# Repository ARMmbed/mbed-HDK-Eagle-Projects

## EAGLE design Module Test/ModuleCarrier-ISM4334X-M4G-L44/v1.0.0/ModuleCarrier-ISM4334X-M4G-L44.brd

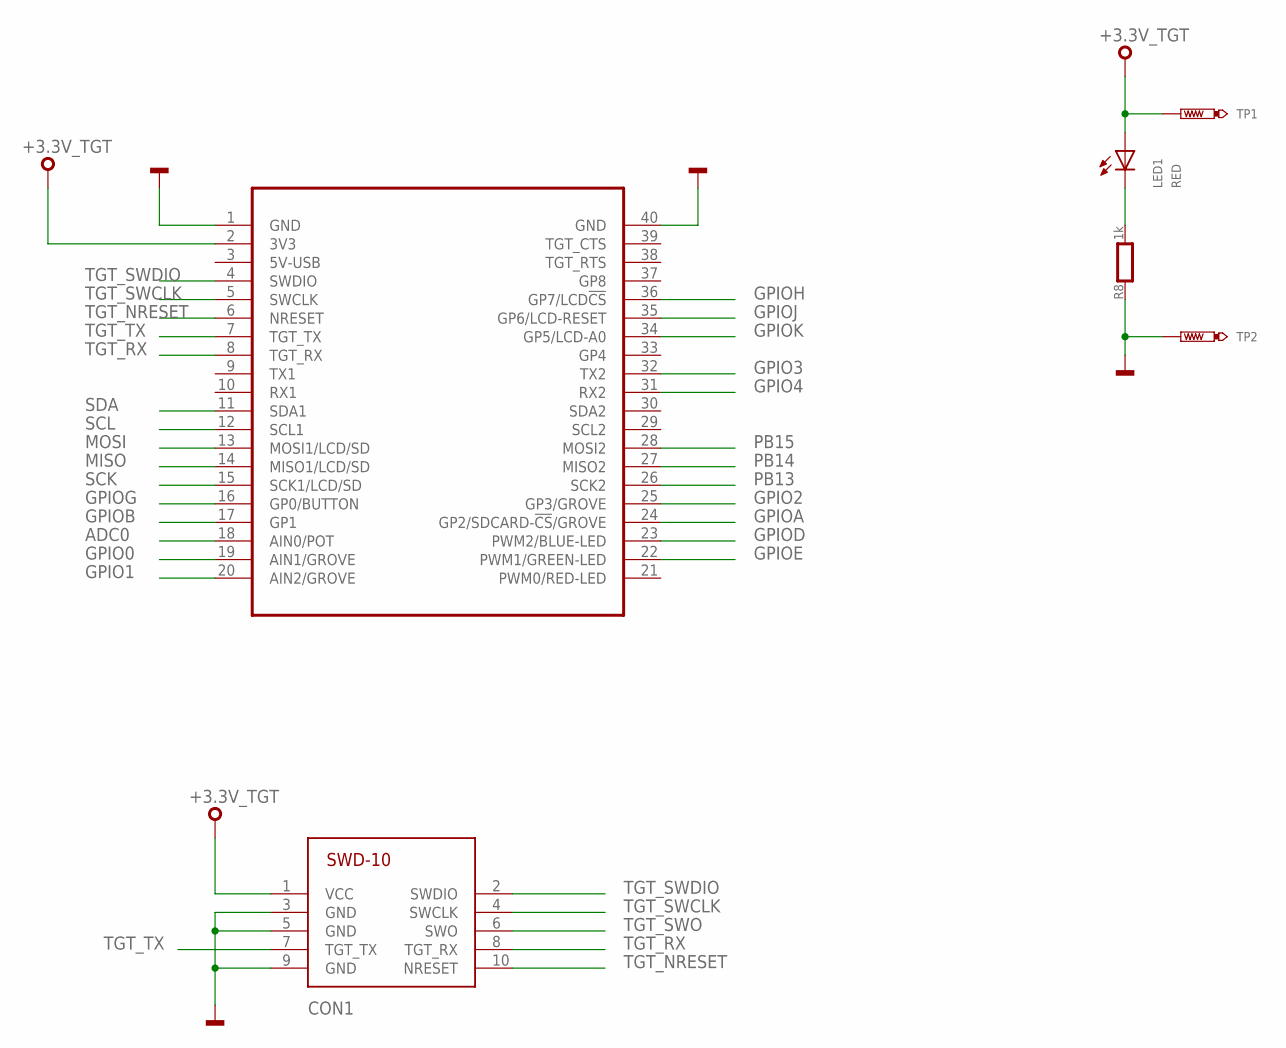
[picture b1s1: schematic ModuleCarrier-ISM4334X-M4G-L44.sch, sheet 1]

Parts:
CON1: SWD-10/TC2050_SMD; FTSH-105-02
LED1: RED; CHIPLED_0603
MOD2: MODULE_DAUGHTER
R8: 1k; 0603
TP1, TP2: TEST-POINT-50R-PTH; TP50-PTH

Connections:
+3.3V_TGT: CON1.1 (VCC), LED1.A, MOD2.2 (3V3), TP1.TP; also elsewhere on the board
ADC0: MOD2.18 (AIN0/POT); also elsewhere on the board
GND: CON1.3 (GND), CON1.5 (GND), CON1.9 (GND), MOD2.1 (GND), MOD2.40 (GND), R8.1, TP2.TP; also elsewhere on the board
GPIO0: MOD2.19 (AIN1/GROVE); also elsewhere on the board
GPIO1: MOD2.20 (AIN2/GROVE); also elsewhere on the board
GPIO2: MOD2.25 (GP3/GROVE); also elsewhere on the board
GPIO3: MOD2.32 (TX2); also elsewhere on the board
GPIO4: MOD2.31 (RX2); also elsewhere on the board
GPIOA: MOD2.24 (GP2/SDCARD-!CS!/GROVE); also elsewhere on the board
GPIOB: MOD2.17 (GP1); also elsewhere on the board
GPIOD: MOD2.23 (PWM2/BLUE-LED); also elsewhere on the board
GPIOE: MOD2.22 (PWM1/GREEN-LED); also elsewhere on the board
GPIOG: MOD2.16 (GP0/BUTTON); also elsewhere on the board
GPIOH: MOD2.36 (GP7/LCD!CS); also elsewhere on the board
GPIOJ: MOD2.35 (GP6/LCD-RESET); also elsewhere on the board
GPIOK: MOD2.34 (GP5/LCD-A0); also elsewhere on the board
MISO: MOD2.14 (MISO1/LCD/SD); also elsewhere on the board
MOSI: MOD2.13 (MOSI1/LCD/SD); also elsewhere on the board
PA_1: LED1.C, R8.2
PB13: MOD2.26 (SCK2); also elsewhere on the board
PB14: MOD2.27 (MISO2); also elsewhere on the board
PB15: MOD2.28 (MOSI2); also elsewhere on the board
SCK: MOD2.15 (SCK1/LCD/SD); also elsewhere on the board
SCL: MOD2.12 (SCL1); also elsewhere on the board
SDA: MOD2.11 (SDA1); also elsewhere on the board
TGT_NRESET: CON1.10 (NRESET), MOD2.6 (NRESET); also elsewhere on the board
TGT_RX: CON1.8 (TGT_RX), MOD2.8 (TGT_RX); also elsewhere on the board
TGT_SWCLK: CON1.4 (SWCLK), MOD2.5 (SWCLK); also elsewhere on the board
TGT_SWDIO: CON1.2 (SWDIO), MOD2.4 (SWDIO); also elsewhere on the board
TGT_SWO: CON1.6 (SWO); also elsewhere on the board
TGT_TX: CON1.7 (TGT_TX), MOD2.7 (TGT_TX); also elsewhere on the board

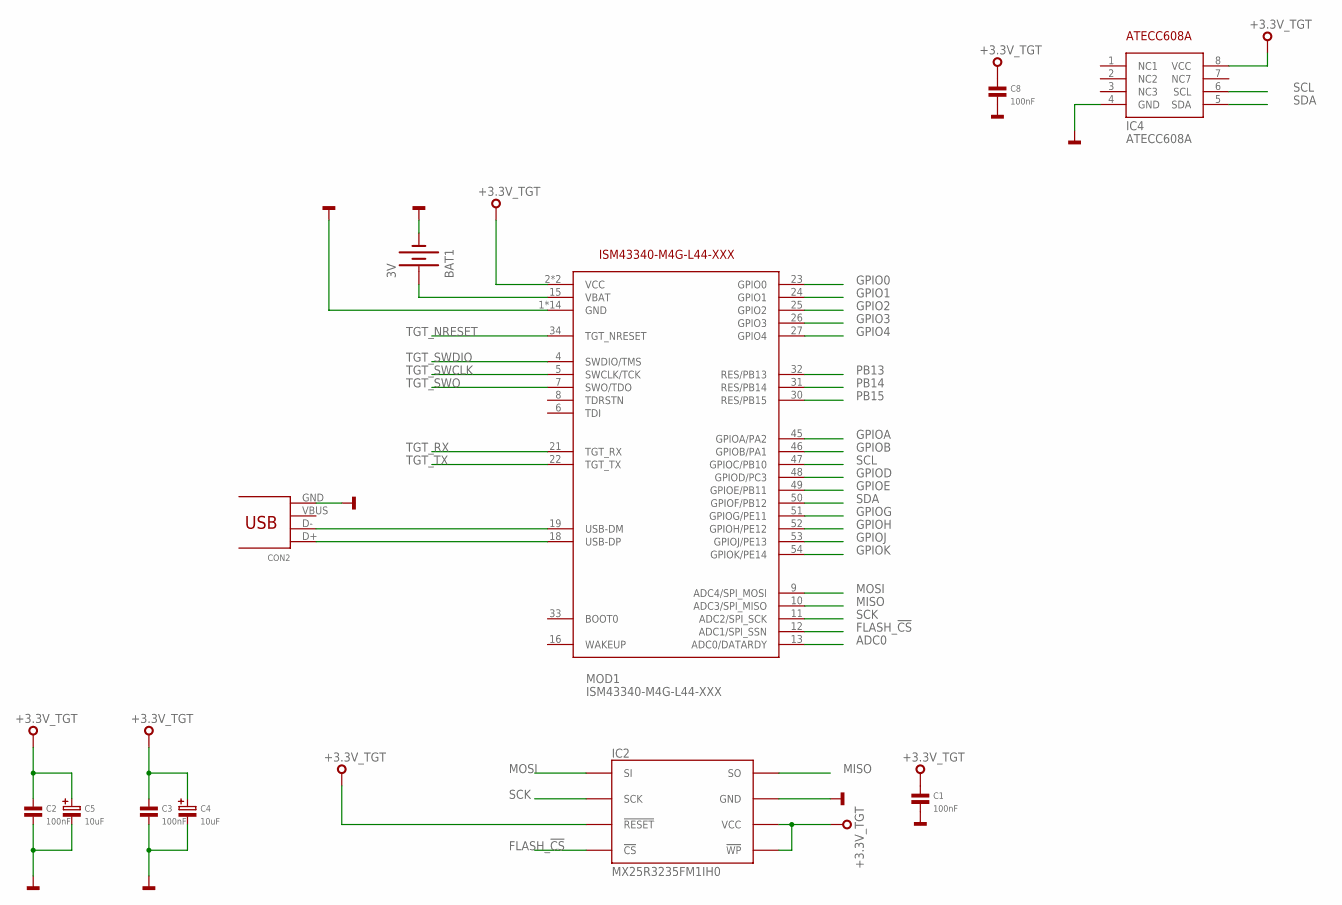
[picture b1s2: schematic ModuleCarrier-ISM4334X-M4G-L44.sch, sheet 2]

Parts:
BAT1: 3V; BATTCON_12MM
C1, C2, C3, C8: 100nF; 0603
C4, C5: 10uF; SMC_B
CON2: 10033526-N3212MLF; USB-MINI-B-H
IC2: MX25R3235FM1IH0; SO8
IC4: ATECC608A; SO8
MOD1: ISM43340-M4G-L44-XXX

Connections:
+3.3V_TGT: C1.1, C2.1, C3.1, C4.+, C5.+, C8.1, IC2.3 (!WP), IC2.7 (!RESET), IC2.8 (VCC), IC4.8 (VCC), MOD1.2 (VCC), MOD1.14 (VCC); also elsewhere on the board
ADC0: MOD1.13 (ADC0/DATARDY); also elsewhere on the board
FLASH_!CS: IC2.1 (!CS), MOD1.12 (ADC1/SPI_SSN)
GND: BAT1.GND (-), C1.2, C2.2, C3.2, C4.-, C5.-, C8.2, CON2.GND, IC2.4 (GND), IC4.4 (GND), MOD1.1 (GND), MOD1.3 (GND), MOD1.17 (GND), MOD1.20 (GND), MOD1.35 (GND), MOD1.36 (GND), MOD1.37 (GND), MOD1.38 (GND), MOD1.39 (GND), MOD1.40 (GND), MOD1.41 (GND), MOD1.42 (GND), MOD1.43 (GND), MOD1.44 (GND); also elsewhere on the board
GPIO0: MOD1.23 (GPIO0); also elsewhere on the board
GPIO1: MOD1.24 (GPIO1); also elsewhere on the board
GPIO2: MOD1.25 (GPIO2); also elsewhere on the board
GPIO3: MOD1.26 (GPIO3); also elsewhere on the board
GPIO4: MOD1.27 (GPIO4); also elsewhere on the board
GPIOA: MOD1.45 (GPIOA/PA2); also elsewhere on the board
GPIOB: MOD1.46 (GPIOB/PA1); also elsewhere on the board
GPIOD: MOD1.48 (GPIOD/PC3); also elsewhere on the board
GPIOE: MOD1.49 (GPIOE/PB11); also elsewhere on the board
GPIOG: MOD1.51 (GPIOG/PE11); also elsewhere on the board
GPIOH: MOD1.52 (GPIOH/PE12); also elsewhere on the board
GPIOJ: MOD1.53 (GPIOJ/PE13); also elsewhere on the board
GPIOK: MOD1.54 (GPIOK/PE14); also elsewhere on the board
MISO: IC2.2 (SO), MOD1.10 (ADC3/SPI_MISO); also elsewhere on the board
MOSI: IC2.5 (SI), MOD1.9 (ADC4/SPI_MOSI); also elsewhere on the board
unnamed: CON2.D+, MOD1.18 (USB-DP)
unnamed: CON2.D-, MOD1.19 (USB-DM)
unnamed: BAT1.PWR@1 (+), MOD1.15 (VBAT)
PB13: MOD1.32 (RES/PB13); also elsewhere on the board
PB14: MOD1.31 (RES/PB14); also elsewhere on the board
PB15: MOD1.30 (RES/PB15); also elsewhere on the board
SCK: IC2.6 (SCK), MOD1.11 (ADC2/SPI_SCK); also elsewhere on the board
SCL: IC4.6 (SCL), MOD1.47 (GPIOC/PB10); also elsewhere on the board
SDA: IC4.5 (SDA), MOD1.50 (GPIOF/PB12); also elsewhere on the board
TGT_NRESET: MOD1.34 (TGT_NRESET); also elsewhere on the board
TGT_RX: MOD1.21 (TGT_RX); also elsewhere on the board
TGT_SWCLK: MOD1.5 (SWCLK/TCK); also elsewhere on the board
TGT_SWDIO: MOD1.4 (SWDIO/TMS); also elsewhere on the board
TGT_SWO: MOD1.7 (SWO/TDO); also elsewhere on the board
TGT_TX: MOD1.22 (TGT_TX); also elsewhere on the board

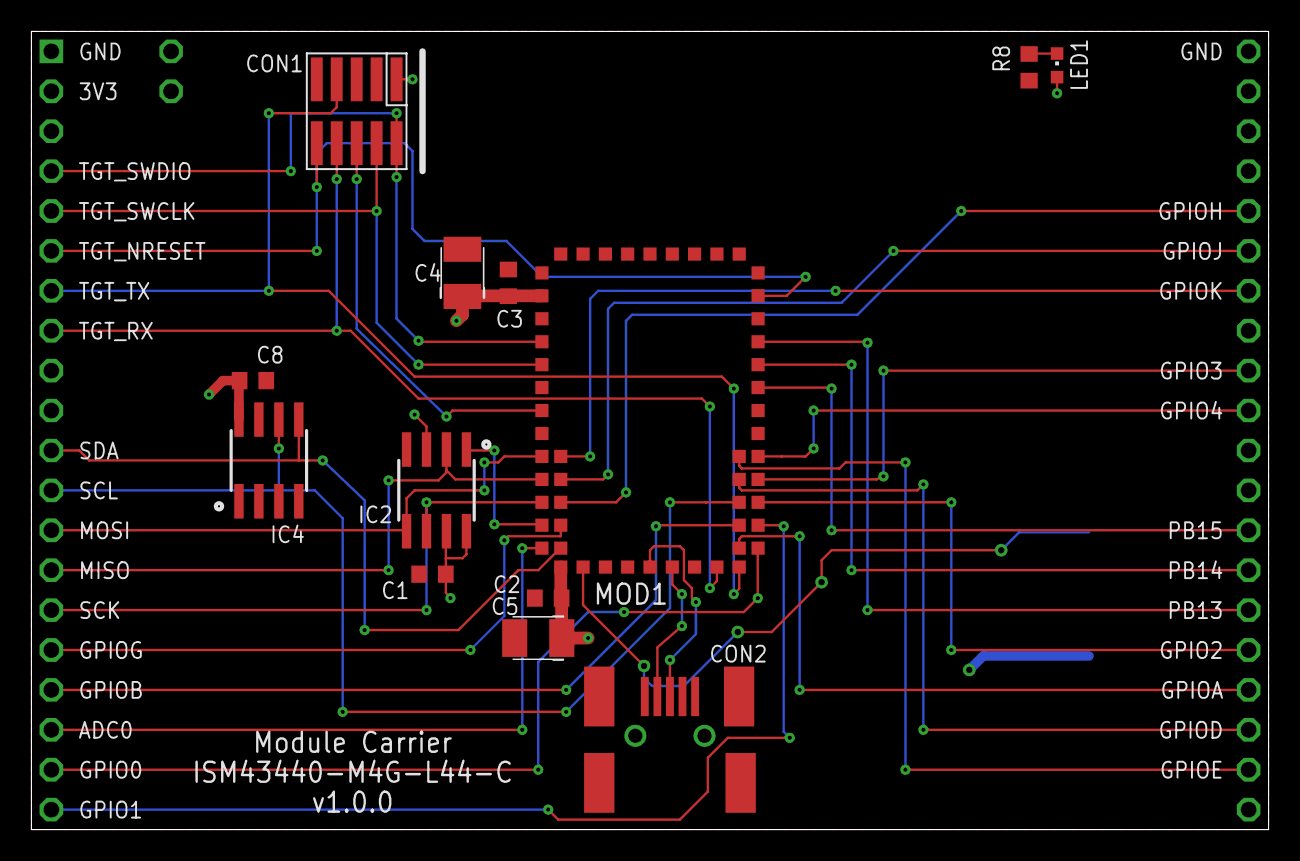
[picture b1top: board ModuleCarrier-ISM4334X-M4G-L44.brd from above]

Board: 2 copper layers, 78.7 x 50.8 mm, 17 parts (1 on the bottom side), 35 nets.

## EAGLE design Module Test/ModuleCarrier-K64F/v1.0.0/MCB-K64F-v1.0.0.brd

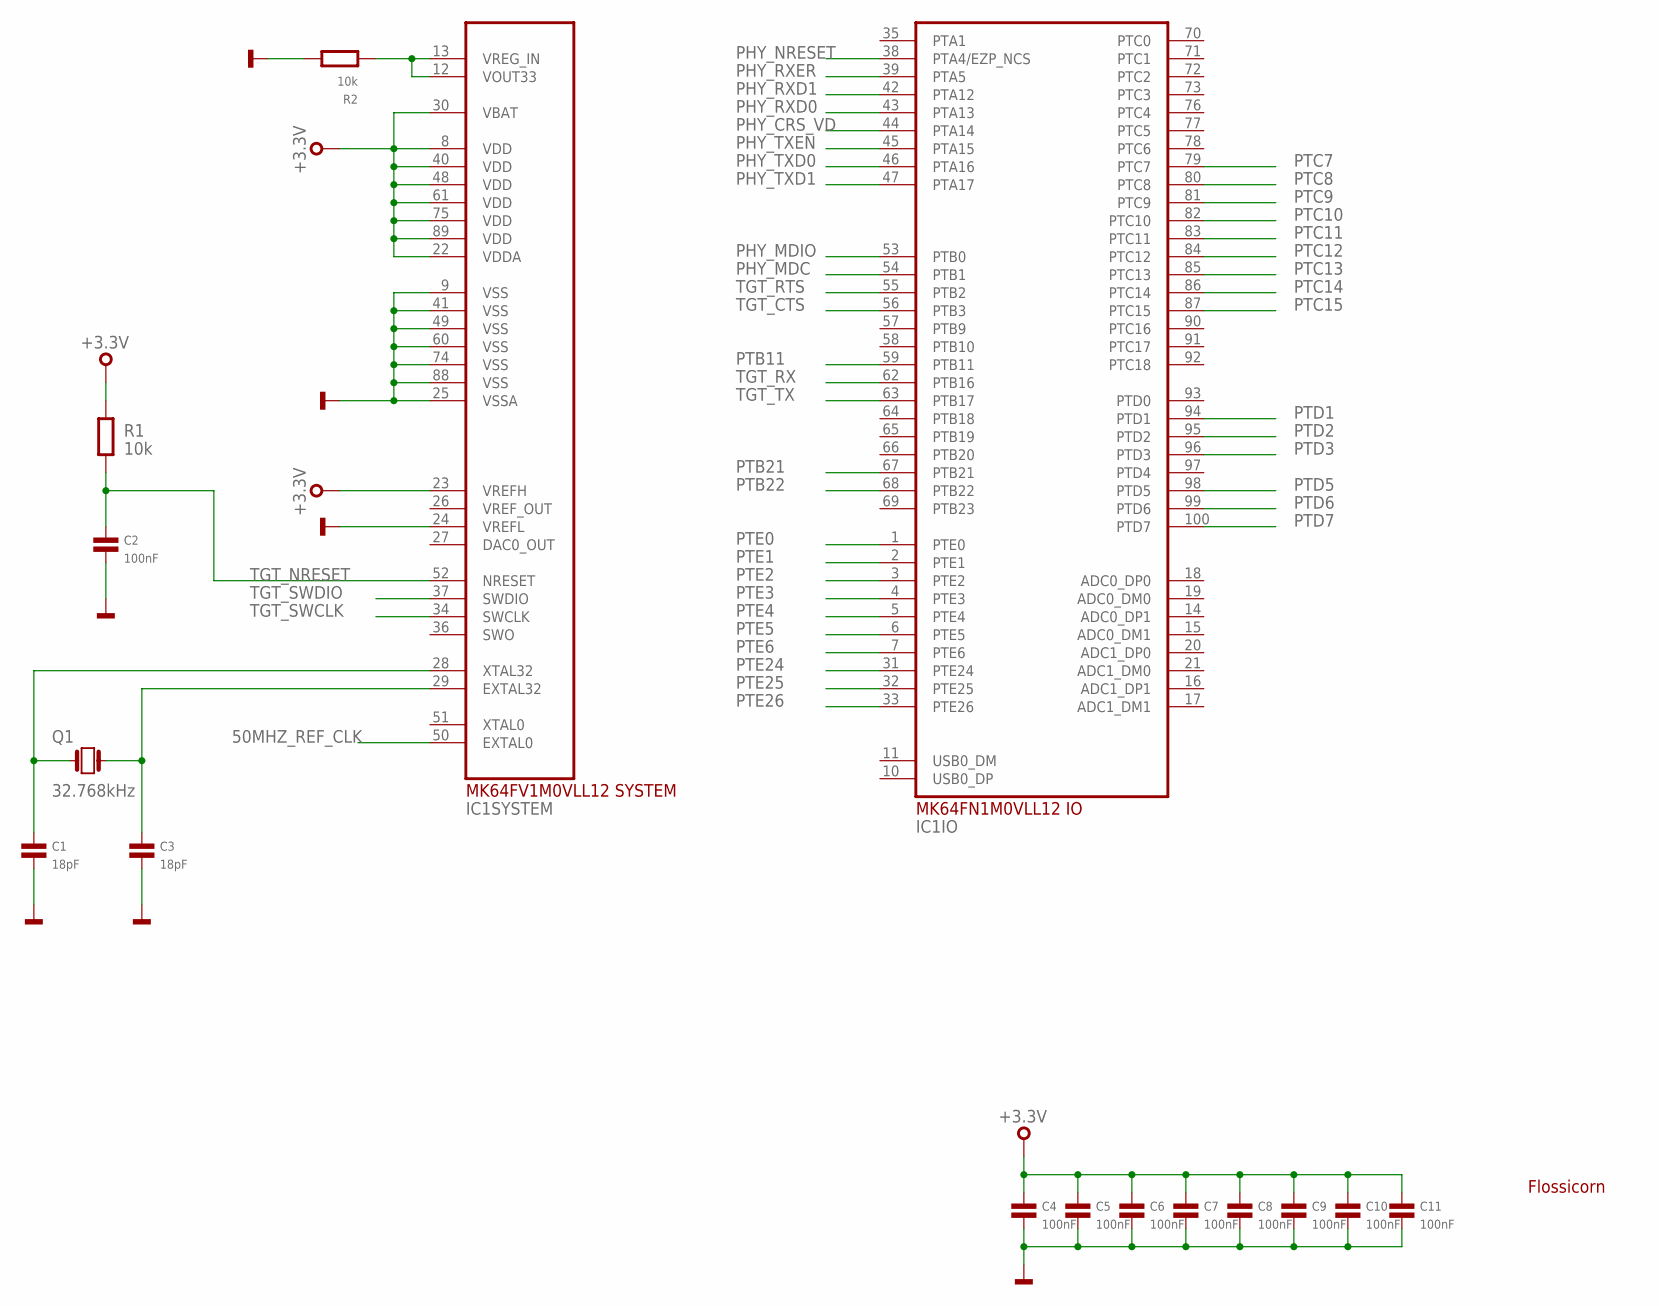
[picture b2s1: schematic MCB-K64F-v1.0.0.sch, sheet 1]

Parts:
C1, C3: 18pF; 0603
C2, C4, C5, C6, C7, C8, C9, C10, C11: 100nF; 0603
IC1: MK64FN1M0VLL12; LQFP100
Q1: 32.768kHz; FC135
R1, R2: 10k; 0603
SS1: FLOSSICORN0.5; FLOSSICORN-0.5

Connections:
50MHZ_REF_CLK: IC1.50 (EXTAL0); also elsewhere on the board
+3.3V: C4.1, C5.1, C6.1, C7.1, C8.1, C9.1, C10.1, C11.1, IC1.8 (VDD), IC1.22 (VDDA), IC1.23 (VREFH), IC1.30 (VBAT), IC1.40 (VDD), IC1.48 (VDD), IC1.61 (VDD), IC1.75 (VDD), IC1.89 (VDD), R1.2; also elsewhere on the board
GND: C1.2, C2.2, C3.2, C4.2, C5.2, C6.2, C7.2, C8.2, C9.2, C10.2, C11.2, IC1.9 (VSS), IC1.24 (VREFL), IC1.25 (VSSA), IC1.41 (VSS), IC1.49 (VSS), IC1.60 (VSS), IC1.74 (VSS), IC1.88 (VSS), R2.2; also elsewhere on the board
unnamed: C1.1, IC1.28 (XTAL32), Q1.X1 (1)
unnamed: C3.1, IC1.29 (EXTAL32), Q1.X2 (2)
unnamed: IC1.12 (VOUT33), IC1.13 (VREG_IN), R2.1
PHY_CRS_VD: IC1.44 (PTA14); also elsewhere on the board
PHY_MDC: IC1.54 (PTB1); also elsewhere on the board
PHY_MDIO: IC1.53 (PTB0); also elsewhere on the board
PHY_NRESET: IC1.38 (PTA4/EZP_NCS); also elsewhere on the board
PHY_RXD0: IC1.43 (PTA13); also elsewhere on the board
PHY_RXD1: IC1.42 (PTA12); also elsewhere on the board
PHY_RXER: IC1.39 (PTA5); also elsewhere on the board
PHY_TXD0: IC1.46 (PTA16); also elsewhere on the board
PHY_TXD1: IC1.47 (PTA17); also elsewhere on the board
PHY_TXEN: IC1.45 (PTA15); also elsewhere on the board
PTB11: IC1.59 (PTB11); also elsewhere on the board
PTB21: IC1.67 (PTB21); also elsewhere on the board
PTB22: IC1.68 (PTB22); also elsewhere on the board
PTC7: IC1.79 (PTC7); also elsewhere on the board
PTC8: IC1.80 (PTC8); also elsewhere on the board
PTC9: IC1.81 (PTC9); also elsewhere on the board
PTC10: IC1.82 (PTC10); also elsewhere on the board
PTC11: IC1.83 (PTC11); also elsewhere on the board
PTC12: IC1.84 (PTC12); also elsewhere on the board
PTC13: IC1.85 (PTC13); also elsewhere on the board
PTC14: IC1.86 (PTC14); also elsewhere on the board
PTC15: IC1.87 (PTC15); also elsewhere on the board
PTD1: IC1.94 (PTD1); also elsewhere on the board
PTD2: IC1.95 (PTD2); also elsewhere on the board
PTD3: IC1.96 (PTD3); also elsewhere on the board
PTD5: IC1.98 (PTD5); also elsewhere on the board
PTD6: IC1.99 (PTD6); also elsewhere on the board
PTD7: IC1.100 (PTD7); also elsewhere on the board
PTE0: IC1.1 (PTE0); also elsewhere on the board
PTE1: IC1.2 (PTE1); also elsewhere on the board
PTE2: IC1.3 (PTE2); also elsewhere on the board
PTE3: IC1.4 (PTE3); also elsewhere on the board
PTE4: IC1.5 (PTE4); also elsewhere on the board
PTE5: IC1.6 (PTE5); also elsewhere on the board
PTE6: IC1.7 (PTE6); also elsewhere on the board
PTE24: IC1.31 (PTE24); also elsewhere on the board
PTE25: IC1.32 (PTE25); also elsewhere on the board
PTE26: IC1.33 (PTE26); also elsewhere on the board
TGT_CTS: IC1.56 (PTB3); also elsewhere on the board
TGT_NRESET: C2.1, IC1.52 (NRESET), R1.1; also elsewhere on the board
TGT_RTS: IC1.55 (PTB2); also elsewhere on the board
TGT_RX: IC1.62 (PTB16); also elsewhere on the board
TGT_SWCLK: IC1.34 (SWCLK); also elsewhere on the board
TGT_SWDIO: IC1.37 (SWDIO); also elsewhere on the board
TGT_TX: IC1.63 (PTB17); also elsewhere on the board

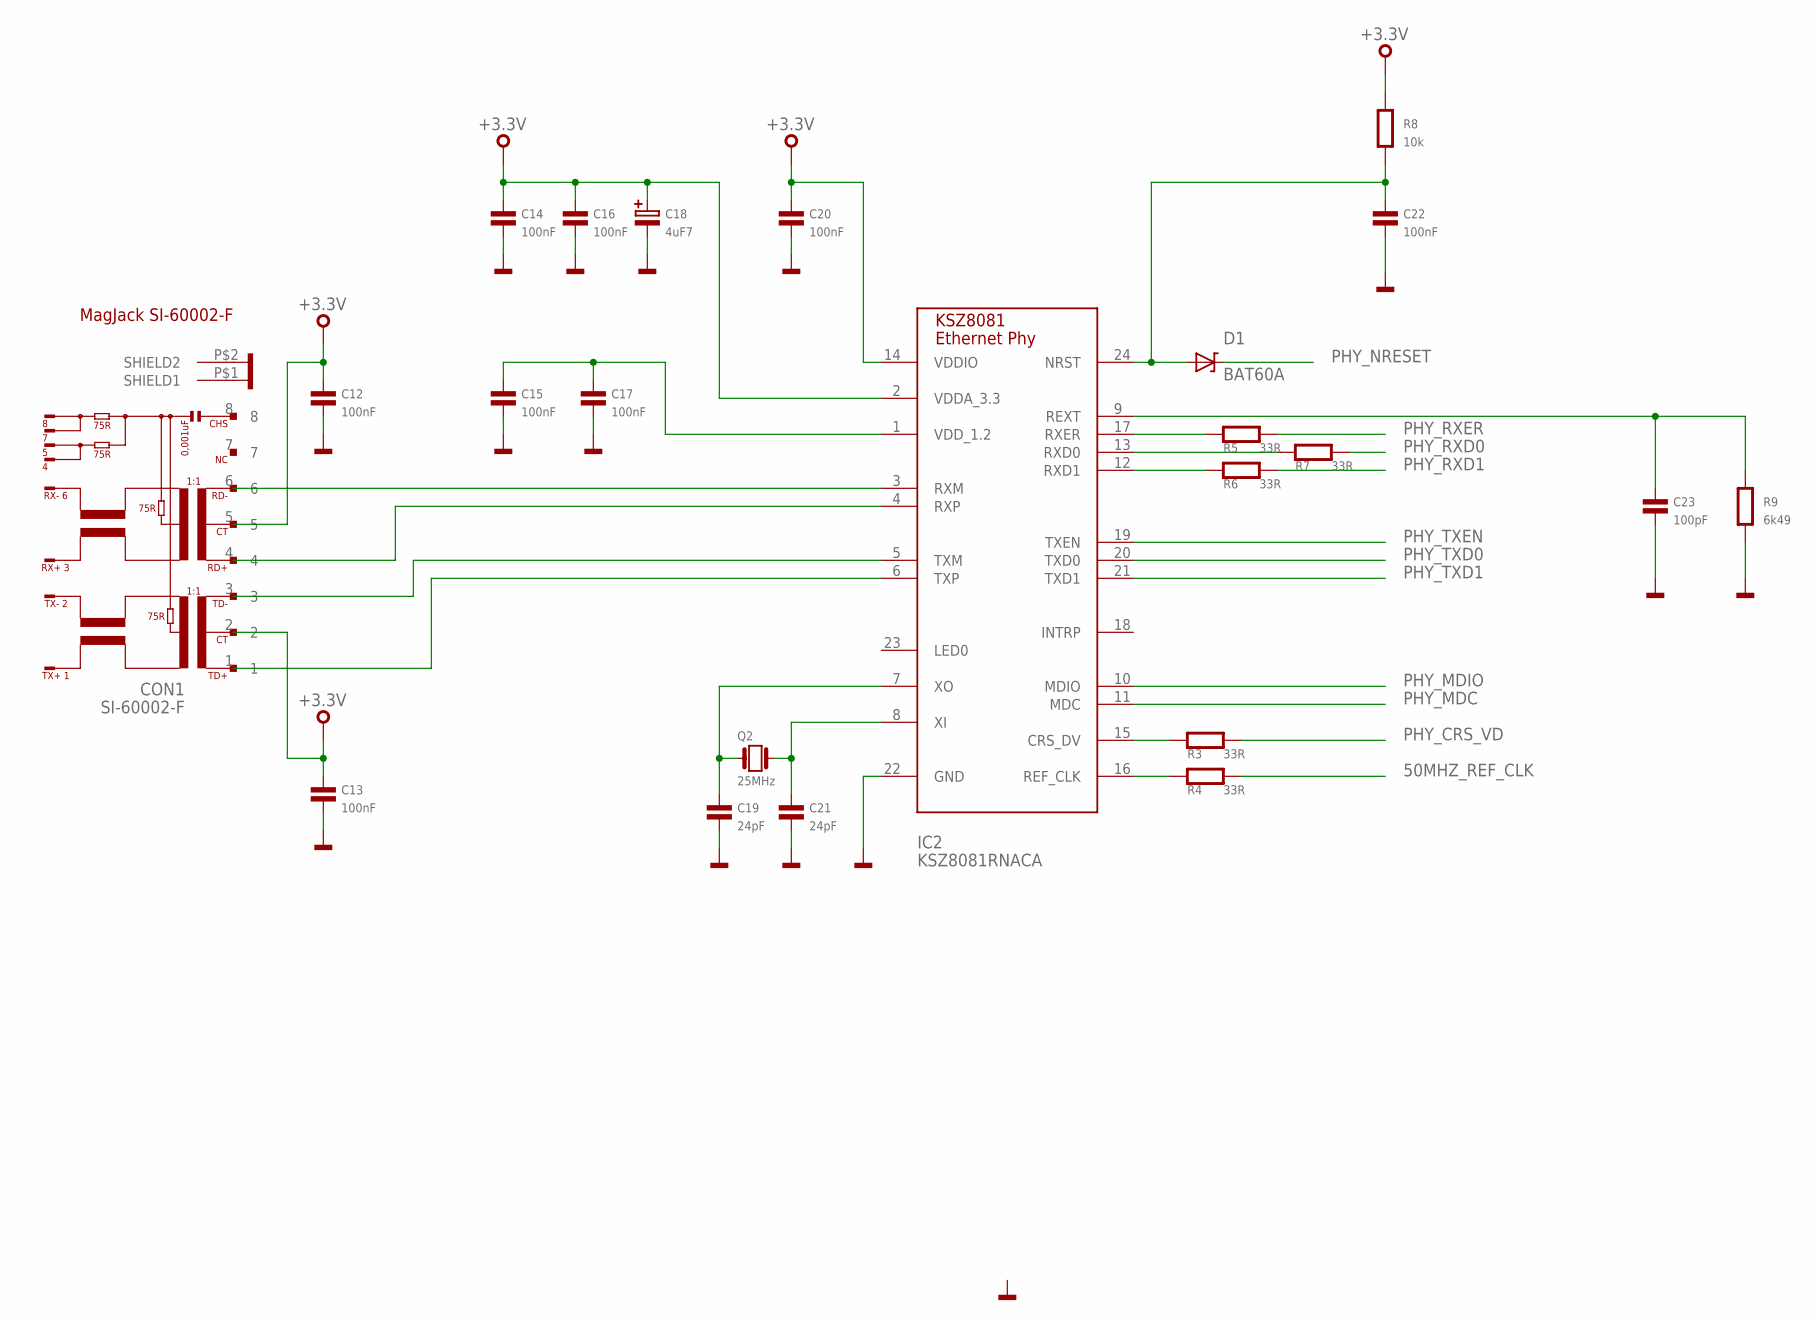
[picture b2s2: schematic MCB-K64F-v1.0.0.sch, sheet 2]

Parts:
C12, C13, C14, C15, C16, C17, C20, C22: 100nF; 0603
C18: 4uF7; SMC_A
C19, C21: 24pF; 0603
C23: 100pF; 0603
CON1: SI-60002-F; RJ45
D1: BAT60A
IC2: KSZ8081RNACA; QFN-24
Q2: 25MHz; 3.2X.2.5
R3, R4, R5, R6, R7: 33R; 0603
R8: 10k; 0603
R9: 6k49; 0603

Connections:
50MHZ_REF_CLK: R4.2; also elsewhere on the board
+3.3V: C12.1, C13.1, C14.1, C16.1, C18.+, C20.1, CON1.2, CON1.5, IC2.2 (VDDA_3.3), IC2.14 (VDDIO), R8.2; also elsewhere on the board
GND: C12.2, C13.2, C14.2, C15.2, C16.2, C17.2, C18.-, C19.2, C20.2, C21.2, C22.2, C23.2, CON1.P$1 (SHIELD1), CON1.P$2 (SHIELD2), IC2.22 (GND), R9.1; also elsewhere on the board
unnamed: IC2.16 (REF_CLK), R4.1
unnamed: CON1.6, IC2.3 (RXM)
unnamed: CON1.4, IC2.4 (RXP)
unnamed: CON1.3, IC2.5 (TXM)
unnamed: CON1.1, IC2.6 (TXP)
unnamed: C19.1, IC2.7 (XO), Q2.P$1 (1)
unnamed: C21.1, IC2.8 (XI), Q2.P$3 (2)
unnamed: IC2.12 (RXD1), R6.1
unnamed: IC2.13 (RXD0), R7.1
unnamed: IC2.17 (RXER), R5.1
unnamed: IC2.15 (CRS_DV), R3.1
unnamed: C22.1, D1.A, IC2.24 (NRST), R8.1
unnamed: C15.1, C17.1, IC2.1 (VDD_1.2)
unnamed: C23.1, IC2.9 (REXT), R9.2
PHY_CRS_VD: R3.2; also elsewhere on the board
PHY_MDC: IC2.11 (MDC); also elsewhere on the board
PHY_MDIO: IC2.10 (MDIO); also elsewhere on the board
PHY_NRESET: D1.K; also elsewhere on the board
PHY_RXD0: R7.2; also elsewhere on the board
PHY_RXD1: R6.2; also elsewhere on the board
PHY_RXER: R5.2; also elsewhere on the board
PHY_TXD0: IC2.20 (TXD0); also elsewhere on the board
PHY_TXD1: IC2.21 (TXD1); also elsewhere on the board
PHY_TXEN: IC2.19 (TXEN); also elsewhere on the board

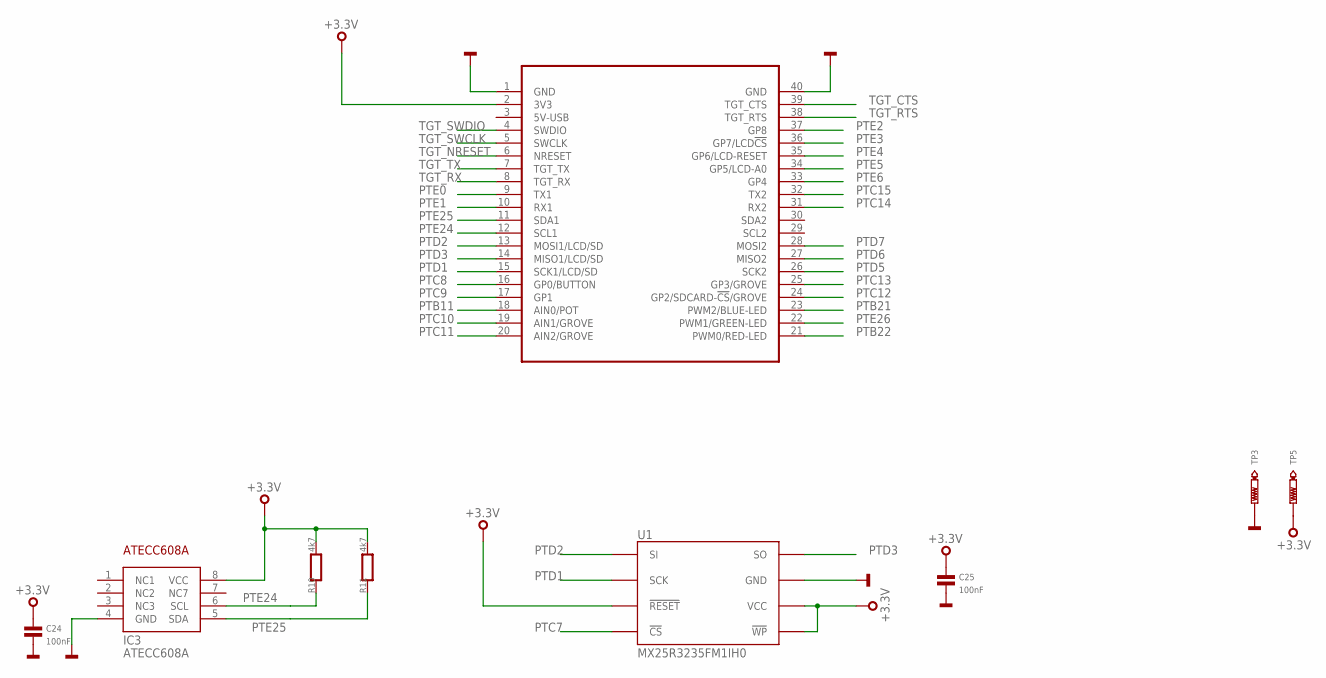
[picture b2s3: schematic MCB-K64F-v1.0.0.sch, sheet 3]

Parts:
C24, C25: 100nF; 0603
IC3: ATECC608A; SO8
MOD1: MODULE_DAUGHTER
R10, R11: 4k7; 0603
TP3, TP5: TEST-POINT-50R-PTH; TP50-PTH
U1: MX25R3235FM1IH0; SO8

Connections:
+3.3V: C24.1, C25.1, IC3.8 (VCC), MOD1.2 (3V3), R10.2, R11.2, TP5.TP, U1.3 (!WP), U1.7 (!RESET), U1.8 (VCC); also elsewhere on the board
GND: C24.2, C25.2, IC3.4 (GND), MOD1.1 (GND), MOD1.40 (GND), TP3.TP, U1.4 (GND); also elsewhere on the board
PTB11: MOD1.18 (AIN0/POT); also elsewhere on the board
PTB21: MOD1.23 (PWM2/BLUE-LED); also elsewhere on the board
PTB22: MOD1.21 (PWM0/RED-LED); also elsewhere on the board
PTC7: U1.1 (!CS); also elsewhere on the board
PTC8: MOD1.16 (GP0/BUTTON); also elsewhere on the board
PTC9: MOD1.17 (GP1); also elsewhere on the board
PTC10: MOD1.19 (AIN1/GROVE); also elsewhere on the board
PTC11: MOD1.20 (AIN2/GROVE); also elsewhere on the board
PTC12: MOD1.24 (GP2/SDCARD-!CS!/GROVE); also elsewhere on the board
PTC13: MOD1.25 (GP3/GROVE); also elsewhere on the board
PTC14: MOD1.31 (RX2); also elsewhere on the board
PTC15: MOD1.32 (TX2); also elsewhere on the board
PTD1: MOD1.15 (SCK1/LCD/SD), U1.6 (SCK); also elsewhere on the board
PTD2: MOD1.13 (MOSI1/LCD/SD), U1.5 (SI); also elsewhere on the board
PTD3: MOD1.14 (MISO1/LCD/SD), U1.2 (SO); also elsewhere on the board
PTD5: MOD1.26 (SCK2); also elsewhere on the board
PTD6: MOD1.27 (MISO2); also elsewhere on the board
PTD7: MOD1.28 (MOSI2); also elsewhere on the board
PTE0: MOD1.9 (TX1); also elsewhere on the board
PTE1: MOD1.10 (RX1); also elsewhere on the board
PTE2: MOD1.37 (GP8); also elsewhere on the board
PTE3: MOD1.36 (GP7/LCD!CS); also elsewhere on the board
PTE4: MOD1.35 (GP6/LCD-RESET); also elsewhere on the board
PTE5: MOD1.34 (GP5/LCD-A0); also elsewhere on the board
PTE6: MOD1.33 (GP4); also elsewhere on the board
PTE24: IC3.6 (SCL), MOD1.12 (SCL1), R10.1; also elsewhere on the board
PTE25: IC3.5 (SDA), MOD1.11 (SDA1), R11.1; also elsewhere on the board
PTE26: MOD1.22 (PWM1/GREEN-LED); also elsewhere on the board
TGT_CTS: MOD1.39 (TGT_CTS); also elsewhere on the board
TGT_NRESET: MOD1.6 (NRESET); also elsewhere on the board
TGT_RTS: MOD1.38 (TGT_RTS); also elsewhere on the board
TGT_RX: MOD1.8 (TGT_RX); also elsewhere on the board
TGT_SWCLK: MOD1.5 (SWCLK); also elsewhere on the board
TGT_SWDIO: MOD1.4 (SWDIO); also elsewhere on the board
TGT_TX: MOD1.7 (TGT_TX); also elsewhere on the board

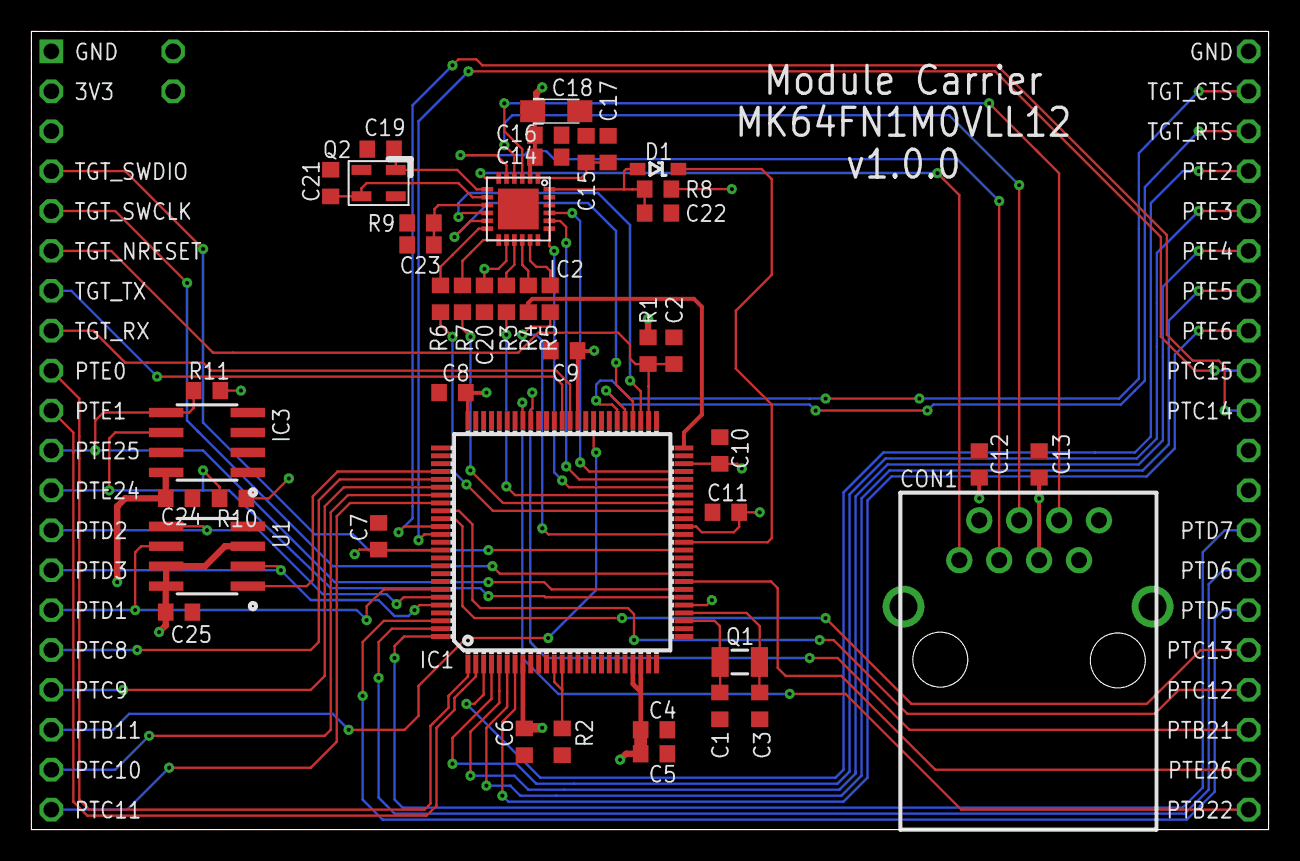
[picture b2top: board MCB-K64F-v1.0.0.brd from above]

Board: 2 copper layers, 78.7 x 50.8 mm, 48 parts (0 on the bottom side), 65 nets.

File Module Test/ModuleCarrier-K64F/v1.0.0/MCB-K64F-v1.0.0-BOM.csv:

"Qty";"Value";"Device";"Package";"Parts";"Description";"MF";"MFN";"OC-DIGIKEY";"OC-MOUSER";"OC-NEWARK";
"17";"100nF";"C0603";"0603";"C2, C4, C5, C6, C7, C8, C9, C10, C11, C12, C13, C14, C15, C16, C17, C20, C22";"Capacitor";"";"";"";"";"";
"2";"100nF";"CAPACITOR0603";"0603";"C24, C25";"Capacitor";"";"";"";"";"";
"1";"100pF";"C0603";"0603";"C23";"Capacitor";"";"";"";"";"";
"3";"10k";"R0603";"0603";"R1, R2, R8";"";"";"";"";"";"";
"2";"18pF";"C0603";"0603";"C1, C3";"Capacitor";"";"";"";"";"";
"2";"24pF";"C0603";"0603";"C19, C21";"Capacitor";"";"";"";"";"";
"1";"25MHz";"Q_3.2X2.5";"3.2X.2.5";"Q2";"";"";"";"";"";"";
"1";"32.768kHz";"Q_FC135";"FC135";"Q1";"";"";"";"";"";"";
"5";"33R";"R0603";"0603";"R3, R4, R5, R6, R7";"";"";"";"";"";"";
"2";"4k7";"RESISTOR0603";"0603";"R10, R11";"Resistor";"";"";"";"";"";
"1";"4uF7";"C-POLA";"SMC_A";"C18";"Polarised capacitor";"";"";"";"";"";
"1";"6k49";"R0603";"0603";"R9";"";"";"";"";"";"";
"1";"ATECC608A";"ATECC608A";"SO8";"IC3";"";"";"";"";"";"";
"1";"BAT60A";"BAT60A";"BAT60A";"D1";"Schottky Diode";"";"";"";"";"";
"1";"FLOSSICORN0.5";"FLOSSICORN0.5";"FLOSSICORN-0.5";"SS1";"";"";"";"";"";"";
"1";"KSZ8081RNACA";"KSZ8081RNACA";"QFN-24";"IC2";"";"";"";"";"";"";
"1";"MK64FN1M0VLL12";"MK64FN1M0VLL12";"LQFP100";"IC1";"";"";"";"";"";"";
"1";"MODULE_DAUGHTER";"MODULE_DAUGHTER";"MODULE_DAUGHTER";"MOD1";"";"";"";"";"";"";
"1";"MX25R3235FM1IH0";"MX25R3235FM1IH0";"SO8";"U1";"Serial Flash 32 Mb 80 Mhz";"Macronix";"MX25R3235FM2IH0";"1092-1174-ND";"";"";
"1";"SI-60002-F";"SI-60002-F";"RJ45";"CON1";"RJ45 Right Angle";"Stewart Connector";"SI-60002-F";"380-1105-ND";"";"24M7449";
"2";"TEST-POINT-50R-PTH";"TEST-POINT-50R-PTH";"TP50-PTH";"TP3, TP5";"";"";"";"";"";"";

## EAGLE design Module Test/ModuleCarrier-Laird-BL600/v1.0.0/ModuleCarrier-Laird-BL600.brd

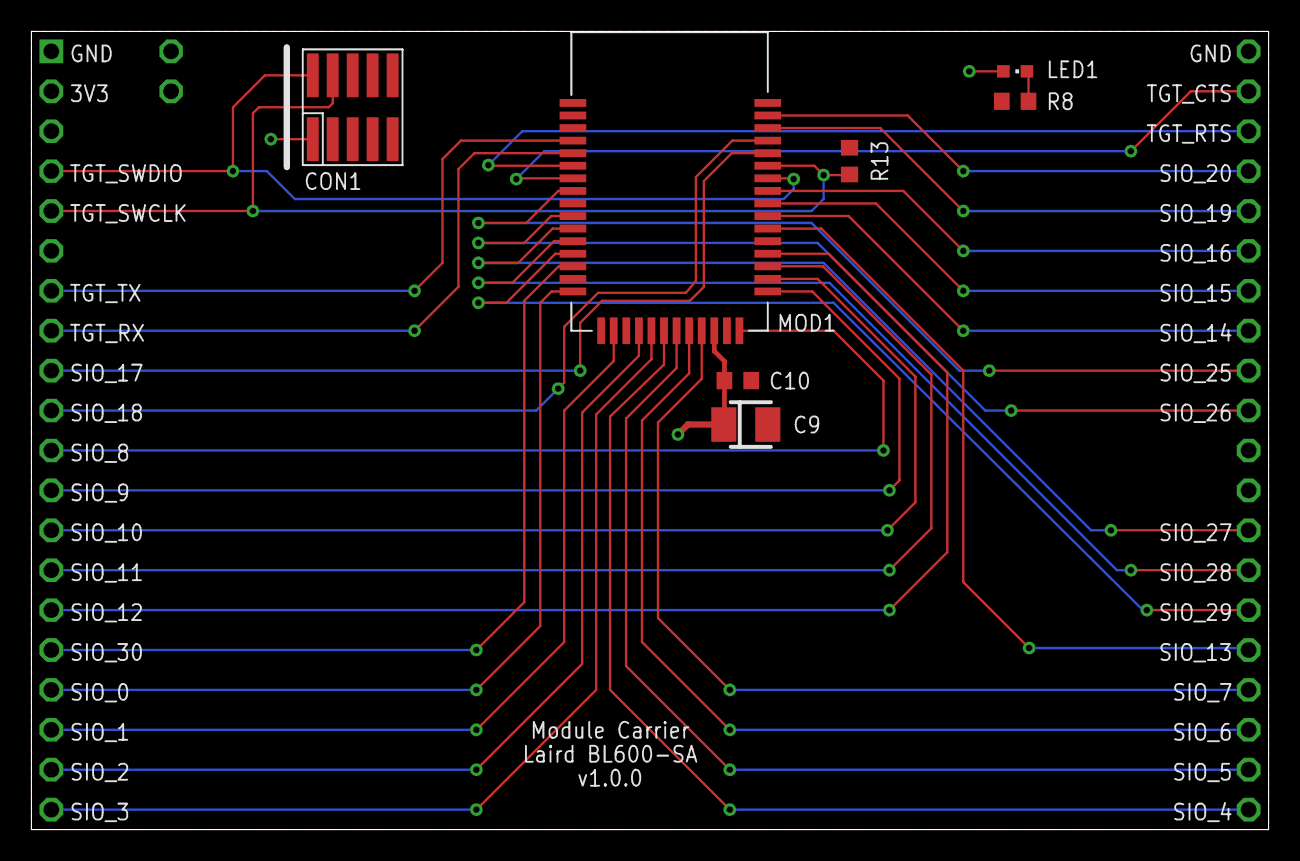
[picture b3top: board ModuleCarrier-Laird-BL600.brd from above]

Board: 2 copper layers, 78.7 x 50.8 mm, 10 parts (0 on the bottom side), 36 nets.

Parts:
C9: 10uF; CASE-B
C10: 100nF; 0603
CON1: SWD-10/TC2050_SMD; FTSH-105-02
LED1: RED; CHIPLED_0603
MOD1: BL600-SA; BL600
R8: 1k; 0603
R13: 12k; 0603
TP1, TP2: TEST-POINT-50R-PTH; TP50-PTH
U$1: MODULE_DAUGHTER

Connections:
+3.3V_TGT: C9.1, C10.1, CON1.1, LED1.A, MOD1.P$10, TP1.TP, U$1.2
GND: C9.2, C10.2, CON1.3, CON1.5, CON1.9, MOD1.P$1, MOD1.P$3, MOD1.P$11, MOD1.P$17, MOD1.P$28, MOD1.P$29, MOD1.P$31, MOD1.P$37, MOD1.P$43, R8.1, R13.1, TP2.TP, U$1.1, U$1.40
PA_1: LED1.C, R8.2
SIO_0: MOD1.P$44, U$1.17
SIO_1: MOD1.P$2, U$1.18
SIO_2: MOD1.P$4, U$1.19
SIO_3: MOD1.P$5, U$1.20
SIO_4: MOD1.P$6, U$1.21
SIO_5: MOD1.P$7, U$1.22
SIO_6: MOD1.P$8, U$1.23
SIO_7: MOD1.P$9, U$1.24
SIO_8: MOD1.P$12, U$1.11
SIO_9: MOD1.P$13, U$1.12
SIO_10: MOD1.P$14, U$1.13
SIO_11: MOD1.P$15, U$1.14
SIO_12: MOD1.P$16, U$1.15
SIO_13: MOD1.P$18, U$1.25
SIO_14: MOD1.P$19, U$1.33
SIO_15: MOD1.P$20, U$1.34
SIO_16: MOD1.P$21, U$1.35
SIO_17: MOD1.P$24, U$1.9
SIO_18: MOD1.P$25, U$1.10
SIO_19: MOD1.P$26, U$1.36
SIO_20: MOD1.P$27, U$1.37
SIO_25: MOD1.P$36, U$1.32
SIO_26: MOD1.P$38, U$1.31
SIO_27: MOD1.P$39, U$1.28
SIO_28: MOD1.P$40, U$1.27
SIO_29: MOD1.P$41, U$1.26
SIO_30: MOD1.P$42, U$1.16
TGT_CTS: MOD1.P$35, U$1.39
TGT_RTS: MOD1.P$34, U$1.38
TGT_RX: MOD1.P$33, U$1.8
TGT_SWCLK: CON1.4, MOD1.P$23, R13.2, U$1.5
TGT_SWDIO: CON1.2, MOD1.P$22, U$1.4
TGT_TX: MOD1.P$32, U$1.7

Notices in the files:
parts and their libraries:
SparkFun-Electromechanical: Licensing: CC v3.0 Share-Alike You are welcome to use this library for commercial purposes.
